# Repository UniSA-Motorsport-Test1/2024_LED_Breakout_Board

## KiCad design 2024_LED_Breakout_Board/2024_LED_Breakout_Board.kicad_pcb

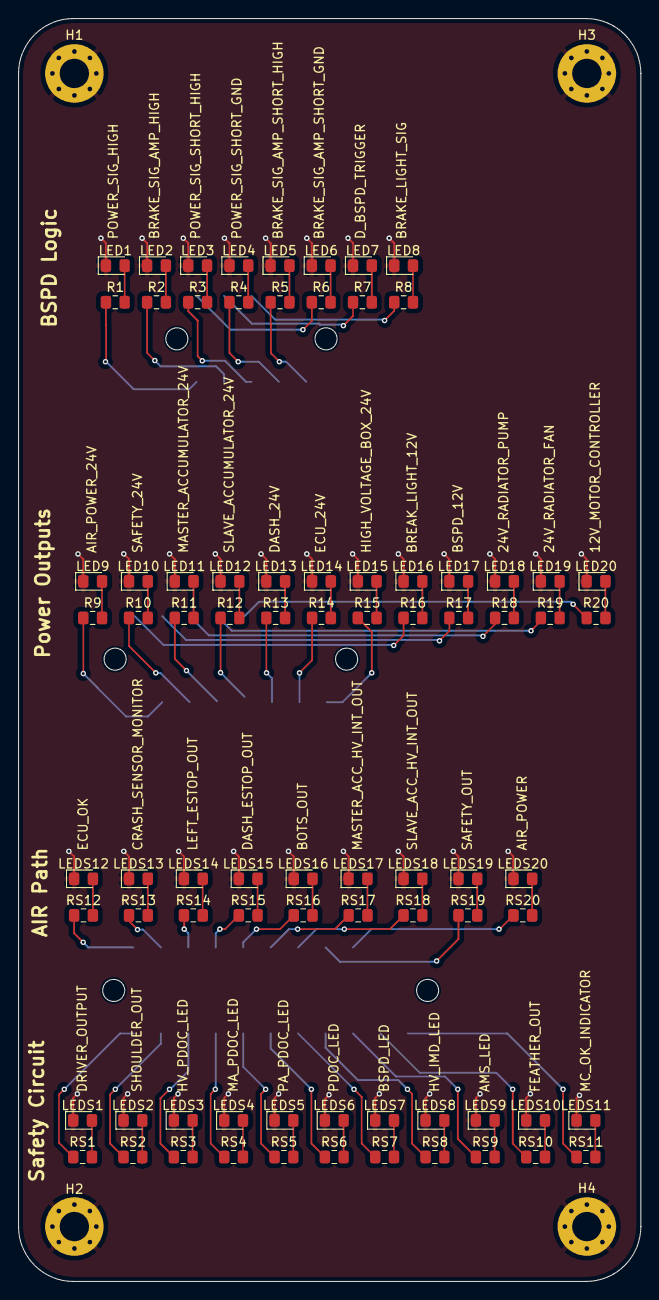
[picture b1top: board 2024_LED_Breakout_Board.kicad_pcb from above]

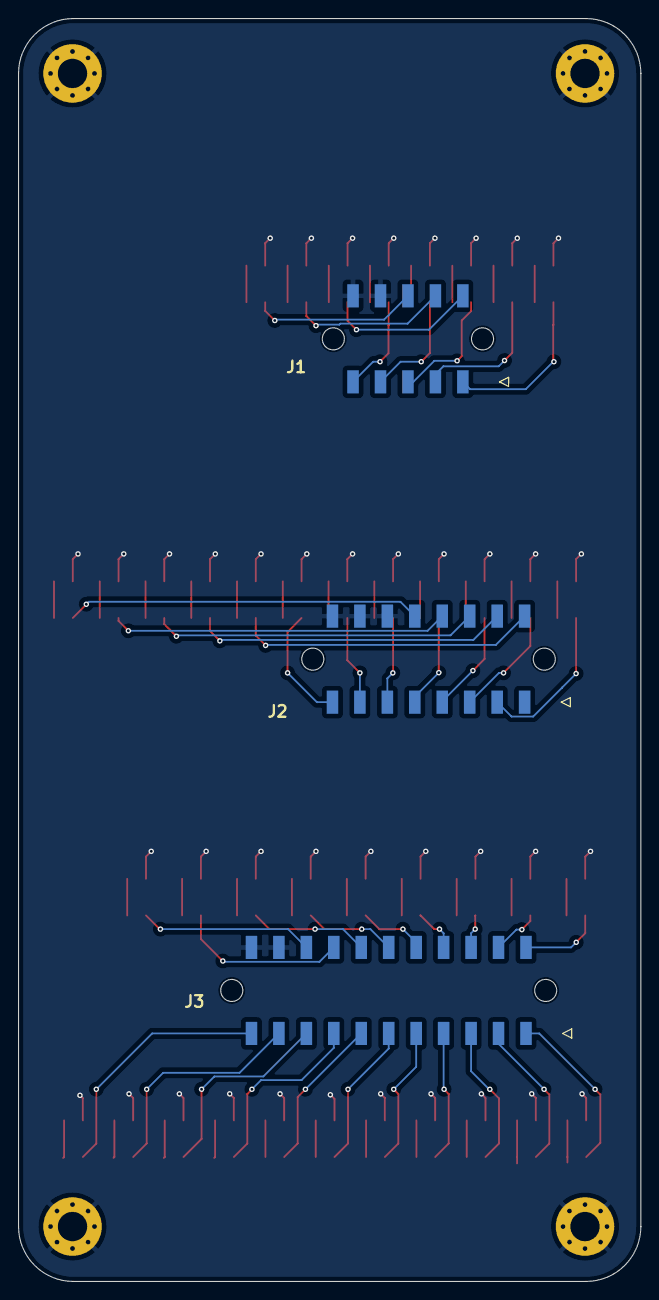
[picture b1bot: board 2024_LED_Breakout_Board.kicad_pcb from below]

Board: 2 copper layers, 68.0 x 138.0 mm, 87 parts (3 on the bottom side), 81 nets.

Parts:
H1, H2, H3, H4: MountingHole_Pad; MountingHole_3.2mm_M3_Pad_Via
J1: 43045-1015; MOLEX_43045-10YY_10PIN
J2: 43045-1615; MOLEX_43045-16YY_16PIN
J3: 43045-2215; MOLEX_43045-22YY_22_PIN
LED1, LED2, LED3, LED4, LED5, LED6, LED8: RED; 0805
LED7, LED9, LED10, LED11, LED12, LED13, LED14, LED15, LED16, LED17, LED18, LED19, LED20: GREEN; 0805
LEDS1, LEDS2, LEDS3, LEDS4, LEDS5, LEDS6, LEDS7, LEDS8, LEDS9, LEDS10, LEDS11, LEDS12: GREEN; 0805
LEDS13, LEDS14, LEDS15, LEDS16, LEDS17, LEDS18, LEDS19, LEDS20: BLUE; 0805
R1, R2, R3, R4, R5, R6, R7, R8, R9, R10, R11, R12, R13, R14, R15, R16, R17, R18, R19, R20: CRCW0805; 0805
RS1, RS2, RS3, RS4, RS5, RS6, RS7, RS8, RS9, RS10, RS11, RS12, RS13, RS14, RS15, RS16, RS17, RS18, RS19, RS20: CRCW0805; 0805

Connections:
/12V_MOTOR_CONTROLLER: J2.13, R20.1
/24V_RADIATOR_FAN: J2.12, R19.1
/24V_RADIATOR_PUMP: J2.11, R18.1
/AIR_POWER: J3.20, RS20.1
/AIR_POWER_24V: J2.2, R9.1
/AMS_LED: J3.9, RS9.1
/BOTS_OUT: J3.16, RS16.1
/BRAKE_LIGHT_SIG: J1.8, R8.1
/BRAKE_SIG_AMP_HIGH: J1.2, R2.1
/BRAKE_SIG_AMP_SHORT_GND: J1.6, R6.1
/BRAKE_SIG_AMP_SHORT_HIGH: J1.5, R5.1
/BREAK_LIGHT_12V: J2.9, R16.1
/BSPD_12V: J2.10, R17.1
/BSPD_LED: J3.7, RS7.1
/CRASH_SENSOR_MONITOR: J3.13, RS13.1
/DASH_24V: J2.6, R13.1
/DASH_ESTOP_OUT: J3.15, RS15.1
/DRIVER_OUTPUT: J3.1, RS1.1
/D_BSPD_TRIGGER: J1.7, R7.1
/ECU_24V: J2.7, R14.1
/ECU_OK: J3.12, RS12.1
/FEATHER_OUT: J3.10, RS10.1
/HIGH_VOLTAGE_BOX_24V: J2.8, R15.1
/HV_IMD_LED: J3.8, RS8.1
/HV_PDOC_LED: J3.3, RS3.1
/LEFT_ESTOP_OUT: J3.14, RS14.1
/MASTER_ACCUMULATOR_24V: J2.4, R11.1
/MASTER_ACC_HV_INT_OUT: J3.17, RS17.1
/MA_PDOC_LED: J3.4, RS4.1
/MC_OK_INDICATOR: J3.11, RS11.1
/PDOC_LED: J3.6, RS6.1
/POWER_SIG_HIGH: J1.1, R1.1
/POWER_SIG_SHORT_GND: J1.4, R4.1
/POWER_SIG_SHORT_HIGH: J1.3, R3.1
/SAFETY_24V: J2.3, R10.1
/SAFTEY_OUT: J3.19, RS19.1
/SA_PDOC_LED: J3.5, RS5.1
/SHOULDER_OUT: J3.2, RS2.1
/SLAVE_ACCUMULATOR_24V: J2.5, R12.1
/SLAVE_ACC_HV_INT_OUT: J3.18, RS18.1
GND: H1.1, H2.1, H3.1, H4.1, J1.9, J1.10, J2.14, J2.15, J2.16, J3.21, J3.22, LED1.1 (K), LED2.1 (K), LED3.1 (K), LED4.1 (K), LED5.1 (K), LED6.1 (K), LED7.1 (K), LED8.1 (K), LED9.1 (K), LED10.1 (K), LED11.1 (K), LED12.1 (K), LED13.1 (K), LED14.1 (K), LED15.1 (K), LED16.1 (K), LED17.1 (K), LED18.1 (K), LED19.1 (K), LED20.1 (K), LEDS1.1 (K), LEDS2.1 (K), LEDS3.1 (K), LEDS4.1 (K), LEDS5.1 (K), LEDS6.1 (K), LEDS7.1 (K), LEDS8.1 (K), LEDS9.1 (K), LEDS10.1 (K), LEDS11.1 (K), LEDS12.1 (K), LEDS13.1 (K), LEDS14.1 (K), LEDS15.1 (K), LEDS16.1 (K), LEDS17.1 (K), LEDS18.1 (K), LEDS19.1 (K), LEDS20.1 (K)
unnamed: LED1.2 (A), R1.2
unnamed: LED2.2 (A), R2.2
unnamed: LED3.2 (A), R3.2
unnamed: LED4.2 (A), R4.2
unnamed: LED5.2 (A), R5.2
unnamed: LED6.2 (A), R6.2
unnamed: LED7.2 (A), R7.2
unnamed: LED8.2 (A), R8.2
unnamed: LED9.2 (A), R9.2
unnamed: LED10.2 (A), R10.2
unnamed: LED11.2 (A), R11.2
unnamed: LED12.2 (A), R12.2
unnamed: LED13.2 (A), R13.2
unnamed: LED14.2 (A), R14.2
unnamed: LED15.2 (A), R15.2
unnamed: LED16.2 (A), R16.2
unnamed: LED17.2 (A), R17.2
unnamed: LED18.2 (A), R18.2
unnamed: LED19.2 (A), R19.2
unnamed: LED20.2 (A), R20.2
unnamed: LEDS1.2 (A), RS1.2
unnamed: LEDS2.2 (A), RS2.2
unnamed: LEDS3.2 (A), RS3.2
unnamed: LEDS4.2 (A), RS4.2
unnamed: LEDS5.2 (A), RS5.2
unnamed: LEDS6.2 (A), RS6.2
unnamed: LEDS7.2 (A), RS7.2
unnamed: LEDS8.2 (A), RS8.2
unnamed: LEDS9.2 (A), RS9.2
unnamed: LEDS10.2 (A), RS10.2
unnamed: LEDS11.2 (A), RS11.2
unnamed: LEDS12.2 (A), RS12.2
unnamed: LEDS13.2 (A), RS13.2
unnamed: LEDS14.2 (A), RS14.2
unnamed: LEDS15.2 (A), RS15.2
unnamed: LEDS16.2 (A), RS16.2
unnamed: LEDS17.2 (A), RS17.2
unnamed: LEDS18.2 (A), RS18.2
unnamed: LEDS19.2 (A), RS19.2
unnamed: LEDS20.2 (A), RS20.2

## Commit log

2024-07-14 LED breakout board
2024-07-14 A few minor fixes
2024-07-15 Further changes added
2024-07-25 added 3d model
2024-07-29 Did some minor tweaks to layout
2024-08-01 Board resized to 68mm
